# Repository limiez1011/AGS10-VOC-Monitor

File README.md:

[air quality monitor-bom.csv](https://github.com/user-attachments/files/27851702/air.quality.monitor-bom.csv)
# AGS10-VOC-Monitor
Battery-powered indoor air quality monitor that reads VOC every 60 seconds and displays it on an e-ink screen.

## Functionality
It uses an AGS10 TVOC sensor which samples the air every 60 seconds, when it's not sampling it goes into a sleep mode where the resistive heater turns off, the PCB includes an MCP73831 which charges LiPo batteries at 0.5A which is perfect for a 500mAh or 800mAh LiPo (1C/0.625C charge rate) The MCU is the seeed studios RP2040 which has a trace going from BATT+ to an ADC pin with a voltage divider so that we can know when to charge the batteries. The sample is then displayed on a 2.66in E-ink which is also updated every 60 seconds, It displays voltage and ppb.

## Bill of Materials
### (2 PCBS)
|Name                       |Purpose              |Quantity|Total Cost (USD)|Link                                                                                                                                                             |Distributor|
|---------------------------|---------------------|--------|----------------|-----------------------------------------------------------------------------------------------------------------------------------------------------------------|-----------|
|Passives                   |Caps,Resistors,Diodes|22      |1.00            | [link](https://jlcpcb.com/parts)                                                                                                                                         |JLCPCB     |
|MICROCHIP MCP73831T-2ATI/OT|lipo charger         |2       |2.40            | [link](https://jlcpcb.com/partdetail/MicrochipTech-MCP73831T_2ATIOT/C14879)                                                                                              |JLCPCB     |
|AGS10                      |VOC sensor           |2       |3.20            | [link](https://jlcpcb.com/partdetail/AGS10/C3012632)                                                                                                                     |JLCPCB     |
|SEEED rp2040               |MCU                  |2       |11.30           | [link](https://www.tme.eu/ro/details/seeed-102010428/kituri-de-dezvoltare-altele/seeed-studio/xiao-rp2040/)                                                              |TME EU     |
|PCB                        |PCBA                 |5       |17.00           | [link](https://jlcpcb.com/pcb-assembly)                                                                                                                                  |JLCPCB     |
|Waveshare 18321            |eink display         |1       |14.28           | [link](https://www.tme.eu/ro/details/wsh-18321/hartie-electronica/waveshare/18321)|TME EU     |

## Photos

## Build photos

## Build Instructions

- Create PCB jig
- Apply solder paste using stencil
- place components
- add to hotplate to melt solder
- solder mcu + eink
- flash firmware by pressing boot and adding the firmware file to the root directory
  and thats all.

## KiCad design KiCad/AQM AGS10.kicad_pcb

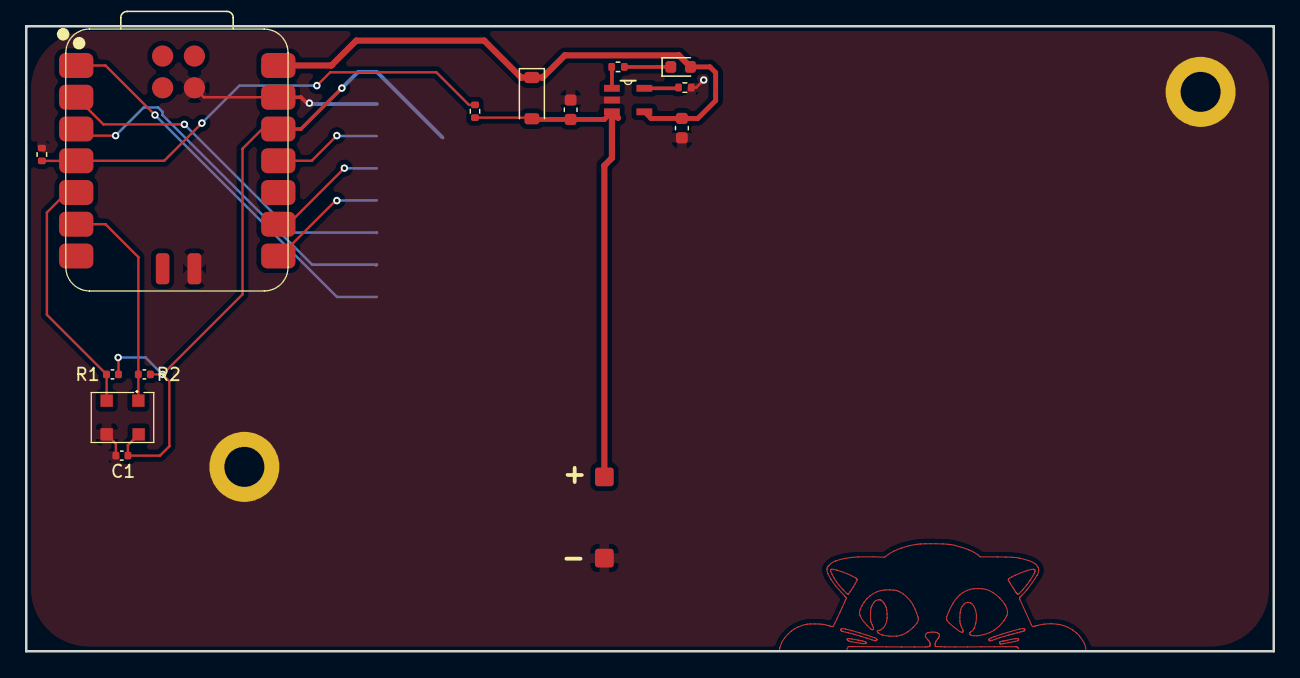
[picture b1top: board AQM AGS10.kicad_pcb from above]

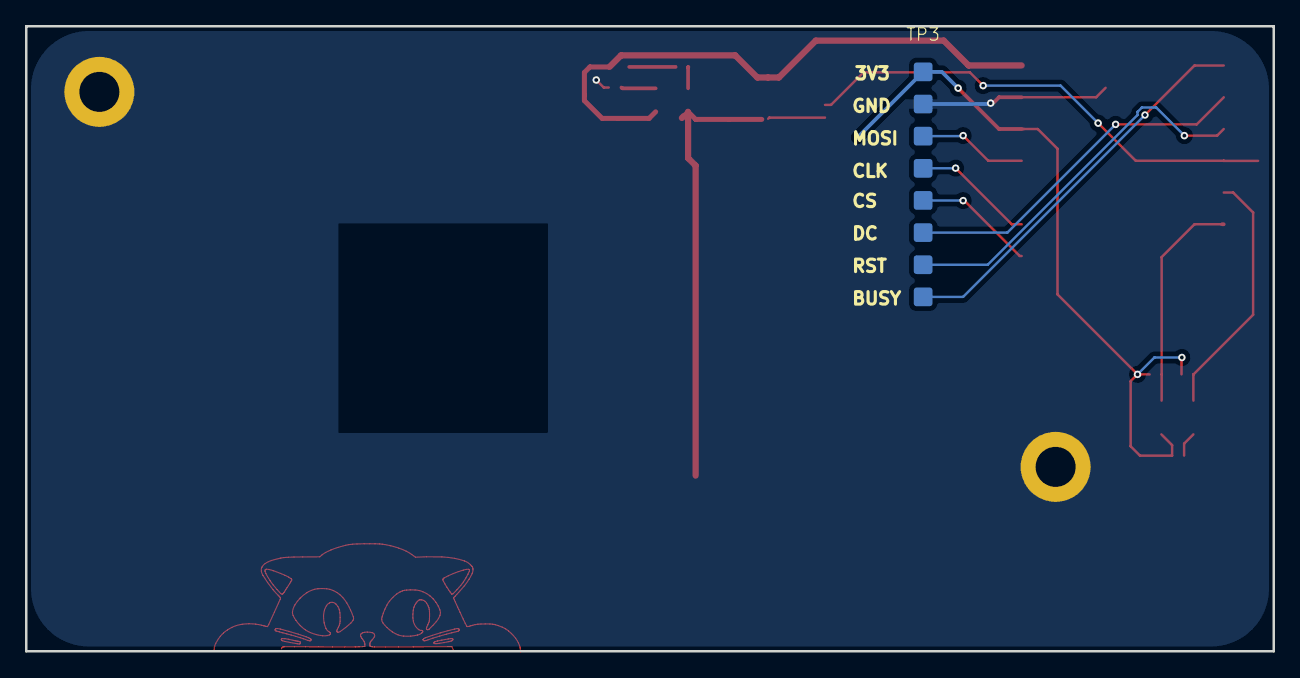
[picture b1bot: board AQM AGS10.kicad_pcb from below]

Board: 2 copper layers, 99.8 x 50.0 mm, 26 parts (8 on the bottom side), 16 nets.

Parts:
C1: 100nF; C_0402_1005Metric
C3, C4: 4.7uF; C_0603_1608Metric
D1: LED_Small; LED_0603_1608Metric
D2: D_Schottky_Small; D_SOD-123
H3, H4: MountingHole_Pad; MountingHole_3.2mm_M3_DIN965_Pad
R1, R2: 4.7K; C_0402_1005Metric
R3: 2K; R_0402_1005Metric
R4: 470; R_0402_1005Metric
R5, R6: 100K; R_0402_1005Metric
TP1: BATT-; padround
TP2, TP3, TP4, TP5, TP6, TP7, TP8, TP9, TP10: BATT+; padround
U1: AGS10
U2: XIAO-RP2040-SMD
U3: MCP73831T-2ACI_OT; SOT95P280X145-5N

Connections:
+3V3: C1.2, R1.1, R2.1, TP3.1 (1_1), U1.4, U2.12 (3V3)
+5V: C3.1, D1.2 (A), D2.1 (K), U2.14 (5V), U3.4 (VDD)
/BAT: C4.1, D2.2 (A), R5.1, TP2.1 (1_1), U3.3 (VBAT)
/BUSY: TP10.1 (1_1), U2.1 (GPIO26_A0_D0)
/CS: TP7.1 (1_1), U2.8 (GPIO1_D7_CSn_RX)
/DC: TP8.1 (1_1), U2.2 (GPIO27_A1_D1)
/MOSI: TP5.1 (1_1), U2.11 (GPIO3_D10_MOSI)
/RST: TP9.1 (1_1), U2.3 (GPIO28_A2_D2)
/SCL: R2.2, U1.1, U2.6 (GPIO7_D5_SCL)
/SCLK: TP6.1 (1_1), U2.9 (GPIO2_D8_SCK)
/SDA: R1.2, U1.2, U2.5 (GPIO6_D4_SDA)
/STAT: R4.2, U3.1 (STAT)
GND: C1.1, C3.2, C4.2, H3.1 (1_1), H4.1 (1_1), R3.2, R6.2, TP1.1 (1_1), TP4.1 (1_1), U1.3, U2.13 (GND), U2.16 (GND), U2.20 (GND), U3.2 (VSS)
unnamed: D1.1 (K), R4.1
unnamed: R5.2, R6.1, U2.4 (GPIO29_A3_D3)
unnamed: R3.1, U3.5 (PROG)

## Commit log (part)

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2026-05-02 Add photos to README for visual reference
    Added photos to the README for better visualization.
2026-05-02 Create x
2026-05-03 Update parts list in README.md
    Added additional components to the parts list.
2026-05-03 Update README with Bill of Materials and photo
    Added detailed Bill of Materials and photo to README.
2026-05-14 Revise Bill of Materials in README
    Updated the Bill of Materials with new components and prices, including total costs and shipping estimates.
2026-05-16 Revise BOM and add external links in README
    Updated the Bill of Materials section and added links to external resources.
2026-05-16 Change PCB quantity in Bill of Materials
    Updated the Bill of Materials section to reflect the quantity of PCBs.
2026-05-16 Format Bill of Materials section in README.md
2026-05-16 Rename air quality monitor-bom (1).csv to BOM.csv
2026-06-04 Add additional images to README
    Added two new images to the Photos section.
2026-06-04 Add new image to README
    Added an additional image to the README.
